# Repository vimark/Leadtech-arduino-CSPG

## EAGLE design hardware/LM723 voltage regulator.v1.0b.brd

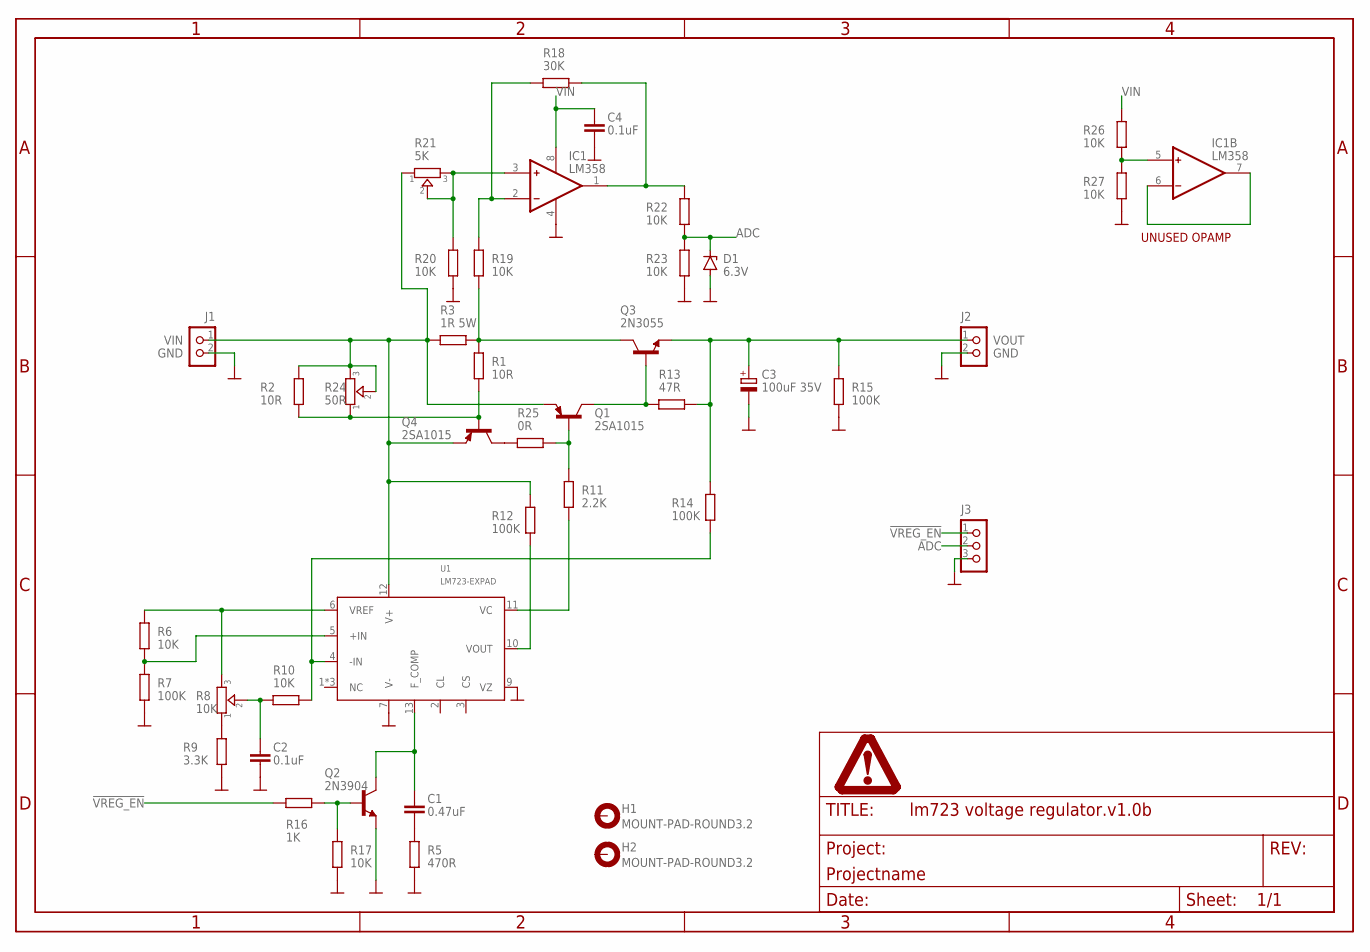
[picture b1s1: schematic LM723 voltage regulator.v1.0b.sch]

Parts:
C1: 0.47uF; C075-042X103
C2, C4: 0.1uF; C075-042X103
C3: 100uF 35V; E2,5-7
D1: 6.3V; DO41Z10
H1, H2: MOUNT-PAD-ROUND3.2; 3,2-PAD
IC1: LM358; DIP8-EXPAD
J1, J2: CON_TERMINAL_BLOCK_02-5MM; TERMINAL_BLOCK_2P_5
J3: CON_HEADER_1X03-PTH; M1X3
PAGE1: FRAME_DINA4_L; DP_LOGO
Q1, Q4: 2SA1015; TO-92
Q2: 2N3904; TO-92
Q3: 2N3055; TO3
R1, R2: 10R; R_5V_EXPAD
R3: 1R 5W; RESISTOR_5W
R5: 470R; R_5V_EXPAD
R6, R17, R19, R20, R22, R23, R26, R27: 10K; R_5V_EXPAD
R7, R12, R14, R15: 100K; R_5V_EXPAD
R8: 10K; TRIMMER_3362P_EXPAD
R9: 3.3K; R_5V_EXPAD
R10: 10K; 0207/12
R11: 2.2K; R_5V_EXPAD
R13: 47R; R_5V_EXPAD
R16: 1K; R-5_EXPAD
R18: 30K; R_5V_EXPAD
R21: 5K; TRIMMER_3362P_EXPAD
R24: 50R; TRIMMER_3362P_EXPAD
R25: 0R; R_5V_EXPAD
U1: LM723-EXPAD; DIP14-EXPAD

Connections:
!VREG_EN: J3.1, R16.1
ADC: D1.C, J3.2, R22.2, R23.1
GND: C2.2, C3.-, C4.2, D1.A, IC1.4 (V-), J1.2, J2.2, J3.3, Q2.1 (E), R5.1, R7.1, R9.1, R15.1, R17.1, R20.2, R23.2, R27.2, U1.7 (V-), U1.9 (VZ)
unnamed: Q3.C, Q3.C/ (C), R1.2, R3.2, R19.2
unnamed: Q4.3 (B), R1.1, R2.1, R24.1
unnamed: Q1.2 (C), Q3.B, R13.1
unnamed: IC1.2 (-), R18.1, R19.1
unnamed: C1.2, R5.2
unnamed: C1.1, Q2.3 (C), U1.13 (F_COMP)
unnamed: R6.1, R7.2, U1.5 (+IN)
unnamed: R6.2, R8.3, U1.6 (VREF)
unnamed: R8.1, R9.2
unnamed: C2.1, R8.2, R10.1
unnamed: R10.2, R14.2, U1.4 (-IN)
unnamed: Q1.3 (B), R11.2, R25.1
unnamed: R11.1, U1.11 (VC)
unnamed: R12.2, U1.10 (VOUT)
unnamed: IC1.3 (+), R20.1, R21.2, R21.3
unnamed: Q2.2 (B), R16.2, R17.2
unnamed: IC1.1 (OUT), R18.2, R22.1
unnamed: Q4.2 (C), R25.2
unnamed: IC1.6 (-), IC1.7 (OUT)
unnamed: IC1.5 (+), R26.2, R27.1
VIN: C4.1, IC1.8 (V+), J1.1, Q1.1 (E), Q4.1 (E), R2.2, R3.1, R12.1, R21.1, R24.2, R24.3, R26.1, U1.12 (V+)
VOUT: C3.+, J2.1, Q3.E, R13.2, R14.1, R15.2

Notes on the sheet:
UNUSED OPAMP

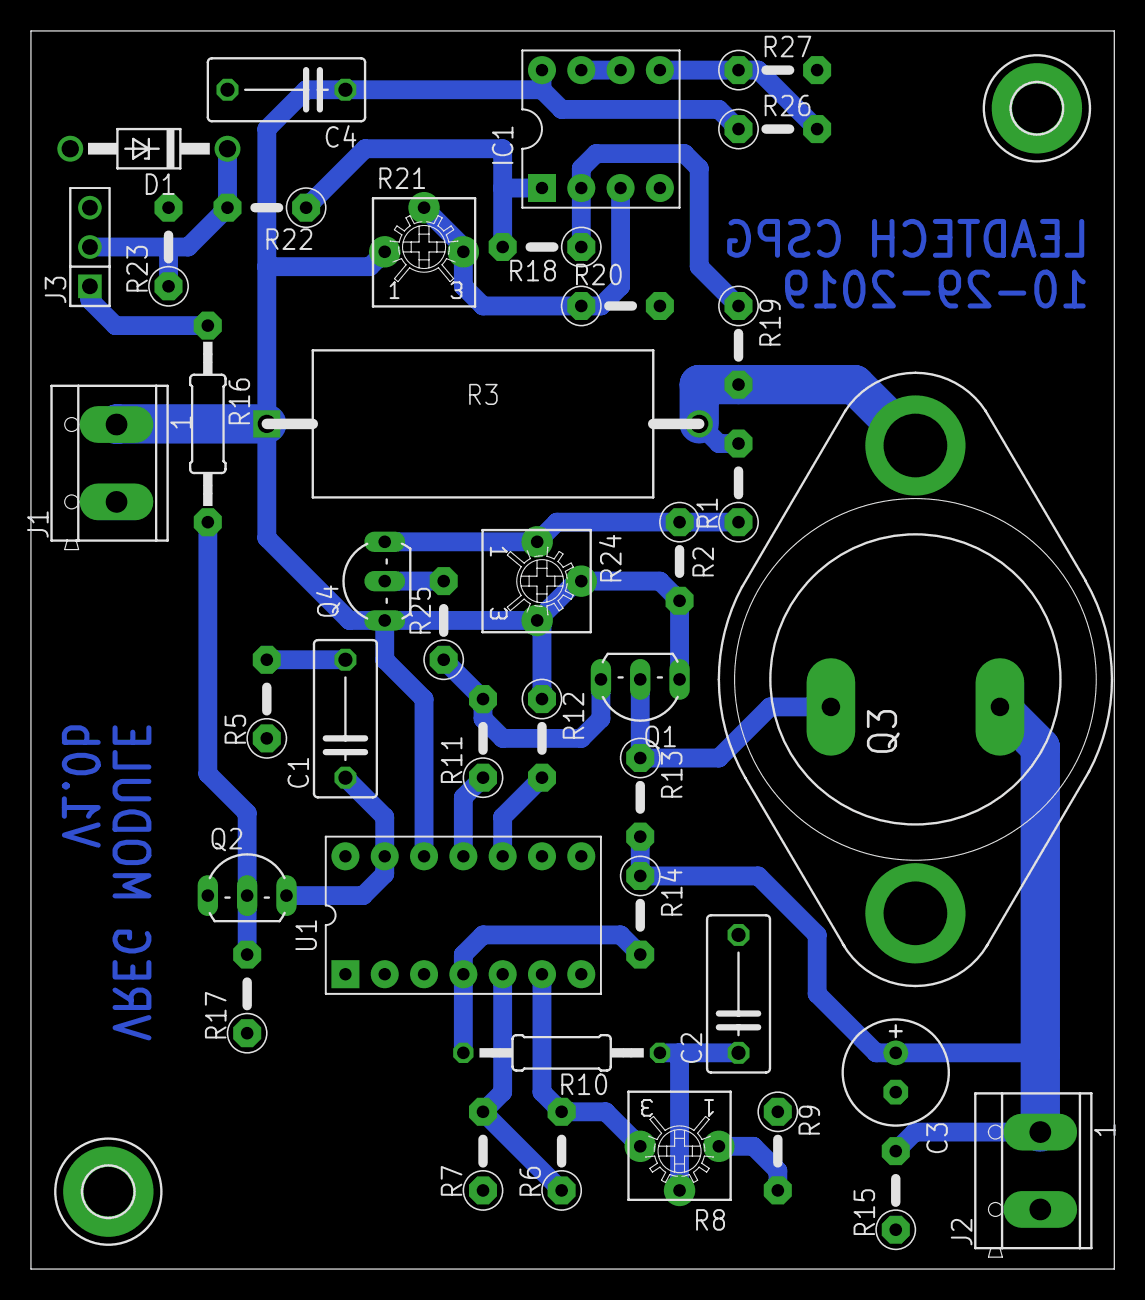
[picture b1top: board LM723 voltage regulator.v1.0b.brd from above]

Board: 2 copper layers, 70.0 x 80.0 mm, 43 parts (0 on the bottom side), 25 nets.

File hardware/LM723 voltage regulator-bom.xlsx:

Qty | Value | Device | Package | Parts | Description | LCSC
2 | 0.1uF | C-EU075-042X103 | C075-042X103 | C2, C4 | CAPACITOR, European symbol | C490602
1 | 0.47uF | C-EU075-042X103 | C075-042X103 | C1 | CAPACITOR, European symbol
1 | 0R | RESISTOR-V | R_5V_EXPAD | R25
4 | 100K | RESISTOR-V | R_5V_EXPAD | R7, R12, R14, R15 |  | C120103 | CF1/4W-100KΩ±5% T52 | CCO(Chian Chia Elec) | 4.875E-3
1 | 100uF 35V | CPOL-EUE2.5-7 | E2,5-7 | C3 | POLARIZED CAPACITOR, European symbol
1 | 10K | R-EU_0207/12 | 0207/12 | R10 | RESISTOR, European symbol | C433778 | RD 1/4W 10K J T/B A1 | TyoHM | 6.0039999999999998E-3
8 | 10K | RESISTOR-V | R_5V_EXPAD | R6, R17, R19, R20, R22, R23, R26, R27 |  | C433778 | RD 1/4W 10K J T/B A1 | TyoHM | 6.0039999999999998E-3
2 | 10R | RESISTOR-V | R_5V_EXPAD | R1, R2 |  | C433800 | RD 1/2WS 10R J T/B A1 | TyoHM RD | 6.0039999999999998E-3
1 | 1K | RESISTOR | R-5_EXPAD | R16
1 | 1R 5W | RESISTOR-5W | RESISTOR_5W | R3 | 22 x 9.5 mm cement resistor
1 | 2.2K | RESISTOR-V | R_5V_EXPAD | R11
1 | 2N3055 | 2N3055 | TO3 | Q3 | NPN Transistor
1 | 2N3904 | TRANSISTOR_BJT_NPN-TO-92-EBC | TO-92 | Q2 | Most commonly used is SOT23-BEC
2 | 2SA1015 | TRANSISTOR_BJT_PNP-TO-92-ECB | TO-92 | Q1, Q4 | Most commonly used is SOT23-BEC
1 | 3.3K | RESISTOR-V | R_5V_EXPAD | R9
1 | 30K | RESISTOR-V | R_5V_EXPAD | R18
1 | 470R | RESISTOR-V | R_5V_EXPAD | R5 |  | C384220 | WR06X471 JTL | Walsin Tech Corp | 2.101E-3
1 | 47R | RESISTOR-V | R_5V_EXPAD | R13
1 | 50R | TRIMMER-3362P_EXPAD | TRIMMER_3362P_EXPAD | R24 | Trimmer resistor | C124583 | 3362P-1-500LF | BOURNS | 0.204545
1 | 5K | TRIMMER-3362P_EXPAD | TRIMMER_3362P_EXPAD | R21 | Trimmer resistor | C81260 | 3362P-1-502LF | BOURNS | 0.21060599999999999
1 | 10K | TRIMMER-3362P_EXPAD | TRIMMER_3362P_EXPAD | R8 | Trimmer resistor | C118956 | 3362P-1-103 | BOCHEN(Chengdu Guosheng Tech) | 0.13120799999999999
1 | 6.3V | 1N4728 | DO41Z10 | D1 | Z DIODE
1 | CON_HEADER_1X03-PTH | CON_HEADER_1X03-PTH | M1X3 | J3
2 | CON_TERMINAL_BLOCK_02-5MM | CON_TERMINAL_BLOCK_02-5MM | TERMINAL_BLOCK_2P_5 | J1, J2 | 2 poles wire to board terminal block
1 | FRAME_DINA4_L | FRAME_DINA4_L | DP_LOGO | PAGE1 | A4 DP frame
1 | LM358 | IC_OP-AMP_LM358-EXPAD | DIP8-EXPAD | IC1 | Dual op-amp | C383852 | TSV358 | Trusignal Microelec | 0.10634299999999999 | SO-8 General Purpose Amplifiers RoHS
1 | LM723-EXPAD | LM723-EXPAD | DIP14-EXPAD | U1 | LM723 Voltage Regulator
2 | MOUNT-PAD-ROUND3.2 | MOUNT-PAD-ROUND3.2 | 3,2-PAD | H1, H2 | MOUNTING PAD, round

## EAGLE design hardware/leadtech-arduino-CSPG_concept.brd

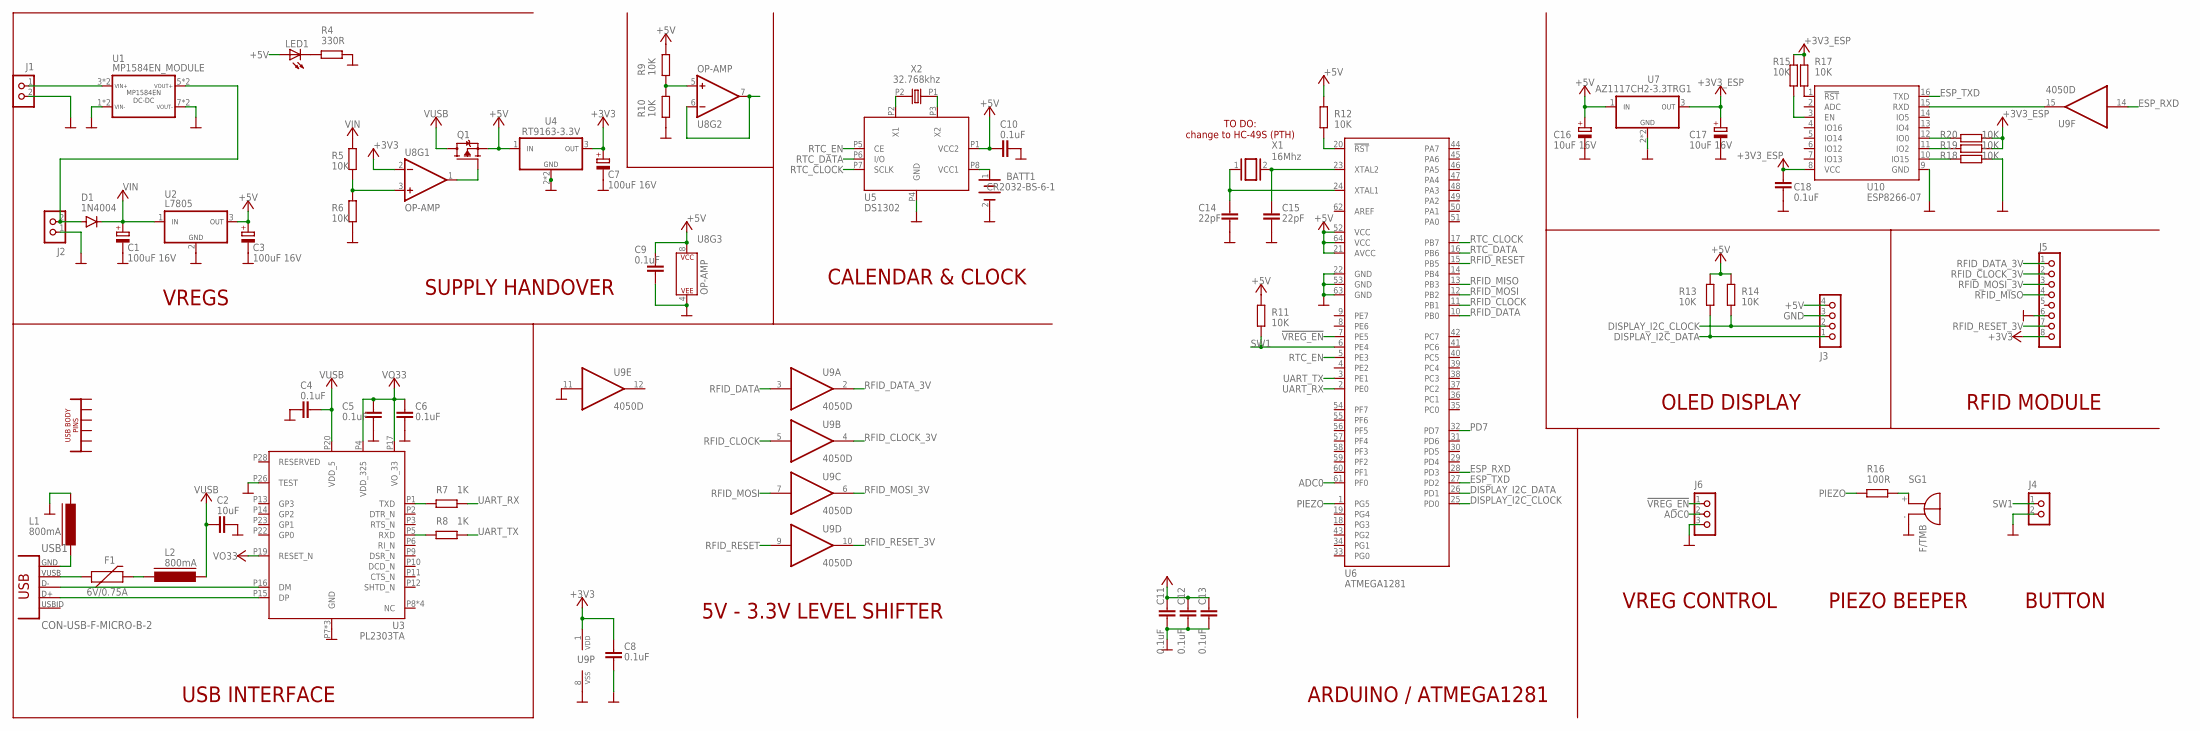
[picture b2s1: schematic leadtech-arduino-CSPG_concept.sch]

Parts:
BATT1: CR2032-BS-6-1; CR2032-BS-6
C1, C3, C7: 100uF 16V; CASE_C
C2: 10uF; C0603
C4, C5, C6, C8, C9, C10, C11, C12, C13, C18: 0.1uF; C0603
C14, C15: 22pF; C0603
C16, C17: 10uF 16V; CASE_B
D1: 1N4004; DO41-10
F1: 6V/0.75A; 1206
J1: CON_HX42003_2; HX42003-2WAF
J2: CON_HEADER_1X02-PTH; M1X2
J3: 2510-4AGW; KF2510-4AGW-2
J4: CON_KF2510-2AGW; KF2510-2AGW
J5: CON_HEADER_1X08-PTH; M1X8
J6: CON_KF2510-3A; KF2510-3A
L1, L2: 800mA; FB805
LED1: LED-0805; LED-805
Q1: TRANSISTOR_FET_TSM2301CX; SOT-23
R4: 330R; R603
R5, R6, R9, R10, R15, R17, R18, R19, R20: 10K; R603
R7, R8: 1K; R603
R11, R12, R13, R14: 10K; R0603
R16: 100R; R0603
SG1: F/TMB
U1: MP1584EN_MODULE; MP1584EN_DCDC_MODULE
U2: L7805; DPAK
U3: PL2303TA; SSOP-28
U4: RT9163-3.3V; SOT-223
U5: DS1302; SOIC-8
U6: ATMEGA1281; TQFP-64
U7: AZ1117CH2-3.3TRG1; SOT-223
U8: OP-AMP; SO08
U9: 4050D; SO16
U10: ESP8266-07
USB1: CON-USB-F-MICRO-B-2; CON_USB_MICRO-B-2-SD-47589-001
X1: 16Mhz; QS
X2: 32.768khz; TC-26

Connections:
!VREG_EN: J6.1, U6.7 (PE5)
+3V3: C7.+, C8.2, J5.8, U4.3 (VOUT), U8.2 (-IN), U9.1 (VDD)
+3V3_ESP: C17.+, C18.2, R15.2, R17.2, R18.1, R19.1, U7.3 (VOUT), U10.8 (VCC)
+5V: C3.+, C9.2, C10.1, C11.1, C12.1, C13.1, C16.+, J3.4, LED1.A, Q1.2 (S), R9.2, R11.2, R12.2, R13.2, R14.2, U2.3 (VOUT), U4.1 (VIN), U5.P1 (VCC2), U6.21 (AVCC), U6.52 (VCC), U6.64 (VCC), U7.1 (VIN), U8.8 (P$V+)
ADC0: J6.2, U6.61 (PF0)
DISPLAY_I2C_CLOCK: J3.2, R14.1, U6.25 (PD0)
DISPLAY_I2C_DATA: J3.1, R13.1, U6.26 (PD1)
ESP_RXD: U6.28 (PD3), U9.14 (I)
ESP_TXD: U6.27 (PD2), U10.16 (TXD)
GND: BATT1.2 (B-), C1.-, C2.1, C3.-, C4.1, C5.2, C6.2, C7.-, C8.1, C9.1, C10.2, C11.2, C12.2, C13.2, C14.1, C15.1, C16.-, C17.-, C18.1, J1.2, J2.1, J3.3, J4.2, J5.6, J6.3, L1.1, R4.2, R6.1, R10.1, R20.1, SG1.-, U1.1 (VIN-), U1.2 (VIN-), U1.7 (VOUT-), U1.8 (VOUT-), U2.2 (GND), U3.P7 (GND), U3.P18 (GND), U3.P25 (GND), U3.P26 (TEST), U4.2 (GND), U4.4 (GND), U5.P4 (GND), U6.22 (GND), U6.53 (GND), U6.63 (GND), U7.2 (GND), U7.4 (GND), U8.4 (P$V-), U9.8 (VSS), U9.11 (I), U10.9 (GND)
unnamed: R17.1, U10.1 (!RST)
unnamed: R15.1, U10.3 (EN)
unnamed: R12.1, U6.20 (!RST)
unnamed: Q1.1 (G), U8.1 (OUT)
unnamed: R5.1, R6.2, U8.3 (+IN)
unnamed: U8.6 (-IN), U8.7 (OUT)
unnamed: J1.1, U1.3 (VIN+), U1.4 (VIN+)
unnamed: C15.2, U6.23 (XTAL2), X1.2
unnamed: R9.1, R10.2, U8.5 (+IN)
unnamed: C14.2, U6.24 (XTAL1), X1.1
unnamed: U3.P16 (DM), USB1.P2 (D-)
unnamed: U3.P15 (DP), USB1.P3 (D+)
unnamed: F1.1, USB1.P1 (VUSB)
unnamed: F1.2, L2.2
unnamed: L1.2, USB1.P5 (GND)
unnamed: R7.1, U3.P1 (TXD)
unnamed: R8.1, U3.P5 (RXD)
unnamed: D1.A, J2.2, U1.5 (VOUT+), U1.6 (VOUT+)
unnamed: R16.2, SG1.+
unnamed: LED1.C, R4.1
unnamed: U5.P3 (X2), X2.P1 (1)
unnamed: U5.P2 (X1), X2.P2 (2)
unnamed: BATT1.1 (B+), U5.P8 (VCC1)
unnamed: R20.2, U10.10 (IO15)
unnamed: R19.2, U10.11 (IO2)
unnamed: R18.2, U10.12 (IO0)
unnamed: U9.15 (O), U10.15 (RXD)
PD7: U6.32 (PD7)
PIEZO: R16.1, U6.1 (PG5)
RFID_CLOCK: U6.11 (PB1), U9.5 (I)
RFID_CLOCK_3V: J5.2, U9.4 (O)
RFID_DATA: U6.10 (PB0), U9.3 (I)
RFID_DATA_3V: J5.1, U9.2 (O)
RFID_MISO: J5.4, U6.13 (PB3)
RFID_MOSI: U6.12 (PB2), U9.7 (I)
RFID_MOSI_3V: J5.3, U9.6 (O)
RFID_RESET: U6.15 (PB5), U9.9 (I)
RFID_RESET_3V: J5.7, U9.10 (O)
RTC_CLOCK: U5.P7 (SCLK), U6.17 (PB7)
RTC_DATA: U5.P6 (I/O), U6.16 (PB6)
RTC_EN: U5.P5 (CE), U6.5 (PE3)
SW1: J4.1, R11.1, U6.6 (PE4)
UART_RX: R7.2, U6.2 (PE0)
UART_TX: R8.2, U6.3 (PE1)
VIN: C1.+, D1.C, R5.2, U2.1 (VIN)
VO33: C5.1, C6.1, U3.P4 (VDD_325), U3.P17 (VO_33), U3.P19 (RESET_N)
VUSB: C2.2, C4.2, L2.1, Q1.3 (D), U3.P20 (VDD_5)

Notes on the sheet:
USB INTERFACE
VREGS
CALENDAR & CLOCK
ARDUINO / ATMEGA1281
RFID MODULE
5V - 3.3V LEVEL SHIFTER
TO DO: change to HC-49S (PTH)
OLED DISPLAY
PIEZO BEEPER
SUPPLY HANDOVER
BUTTON
VREG CONTROL

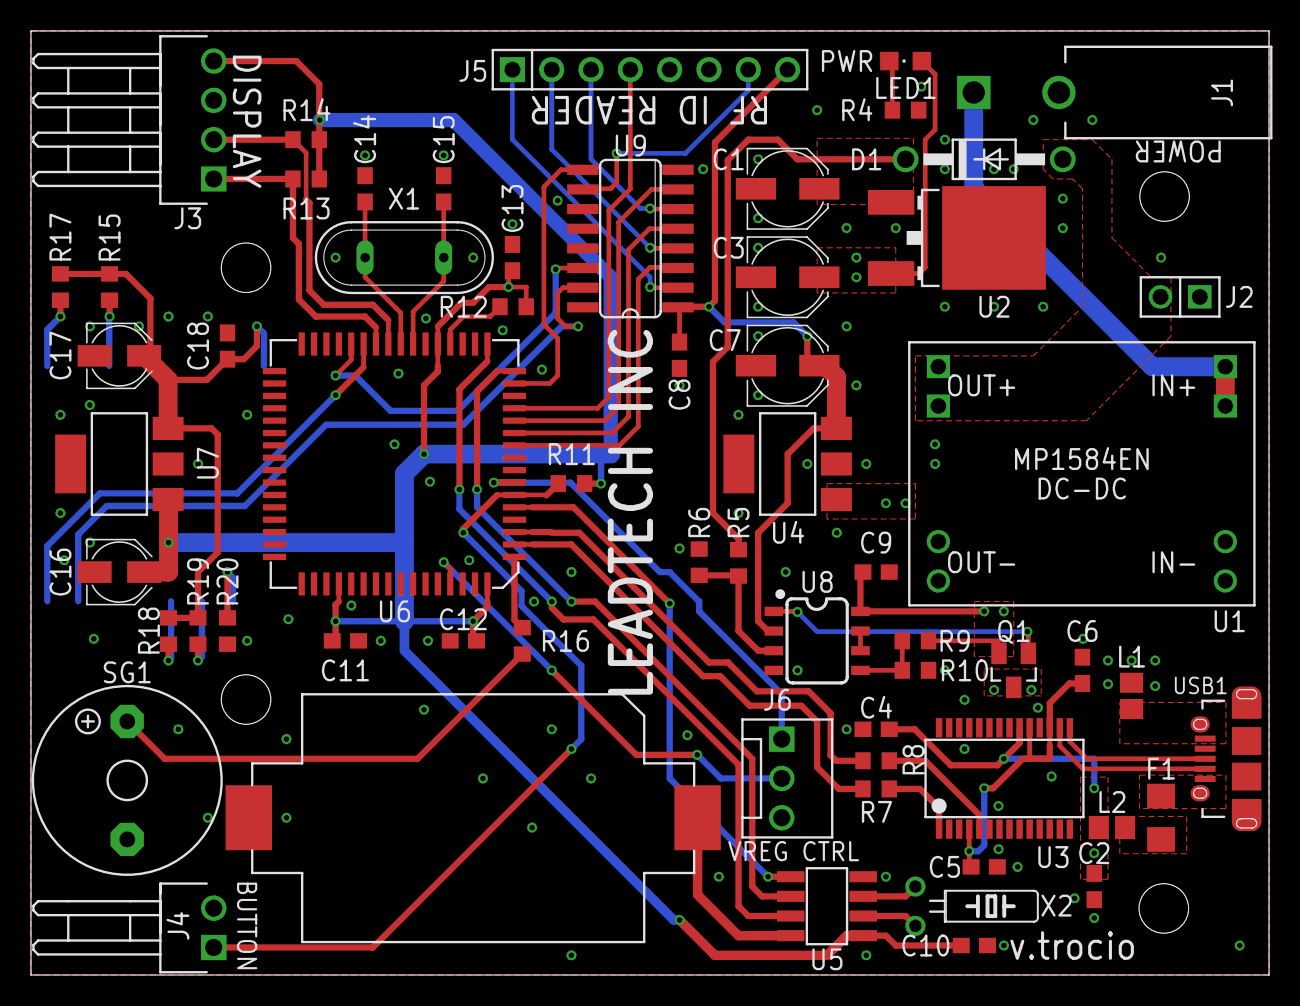
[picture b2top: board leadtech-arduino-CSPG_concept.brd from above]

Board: 2 copper layers, 80.0 x 61.0 mm, 62 parts (1 on the bottom side), 56 nets.

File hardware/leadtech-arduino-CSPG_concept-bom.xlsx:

Qty | Value | Device | Package | Parts | Description | LCSC part no | Mfr no | Brand | Price | Desciption |  | Multiple of 10 | 10
1 |  | LED-0805 | LED-805 | LED1 | Light Emitting Diode | C131244 | 17-21SURC/S530-A2/TR8 | Everlight Elec | 1.4274E-2 |  | 1.4274E-2
1 |  | TRANSISTOR_FET_TSM2301CX | SOT-23 | Q1 | 20V P-Channel Enhancement Mode MOSFET | C375701 | GP2301 | GP(GreenPower) | 3.1213000000000001E-2 |  | 3.1213000000000001E-2
10 | 0.1uF | C-EUC0603 | C0603 | C4, C5, C6, C8, C9, C10, C11, C12, C13, C18 | CAPACITOR, European symbol | C490602 | C0603C104J5RAC | KEMET | 9.2750000000000003E-3 |  | 9.2749999999999999E-2
1 | 100R | R-EU_R0603 | R0603 | R16 | RESISTOR, European symbol | C125923 | AC0603FR-07100RL | YAGEO | 4.202E-3 |  | 4.202E-3
3 | 100uF 16V |  | CASE_C | C1, C3, C7 | Polarized capacitor in various packages | C336761 | EEEFK1C101SR | PANASONIC | 0.171212 |  | 0.51363599999999998
13 | 10K | R-EU_R0603 | R0603 | R11, R12, R13, R14, R5, R6, R9, R10, R15, R17, R18, R19, R20 | RESISTOR, European symbol | C191124 | ERJ3EKF1002V | PANASONIC | 7.8580000000000004E-3 |  | 0.10215400000000001
1 | 10uF | C-EUC0805 | C0603 | C2 | CAPACITOR, European symbol | C76614 | C1608X5R1E106MT000E | TDK | 5.7504E-2 |  | 5.7504E-2
2 | 10uF | CAPACITOR_POL-CASE_B | CASE_B | C16, C17 | Polarized capacitor in various packages | C178278 | EMZA160ADA100MD61G | NCC(Nippon Chemi-Con) | 4.4415000000000003E-2 |  | 8.8830000000000006E-2
1 | 16Mhz | XTAL/S | QS | X1 | CRYSTAL | C114981 | E49A16E00000KE10CO | Hosonic Elec | 0.111524 |  | 0.111524
2 | 1K | RESISTOR-0603 | R603 | R7, R8 |  | C253329 | ESR03EZPJ102 | ROHM Semicon | 1.4148000000000001E-2 |  | 2.8296000000000002E-2
1 | 1N4004 | 1N4004 | DO41-10 | D1 | DIODE | C232435 | 1N4004G | ON Semiconductor | 3.9183999999999997E-2 | 400V 1A 1.1V @ 1A Axial Diodes - General Purpose RoHS | 3.9183999999999997E-2
2 | 22pF | CAPACITOR_NPOL-0805 | C0603 | C14, C15 | Non-Polarized capacitor in various packages | C309441 | AC0603JRNPO9BN220 | YAGEO | 1.6323000000000001E-2 |  | 3.2646000000000001E-2
1 | 2510-4AGW | CON_KF2510-4AGW-2 | KF2510-4AGW-2 | J3 |  | C59729 | 2510-4AGW | BOOMELE(Boom Precision Elec) | 1.8269000000000001E-2 | KF2510 Header Male Pin 0.100"(2.54mm) 4 DIP,P=2.54mm Wire To Board / Wire To Wi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 | 1.8269000000000001E-2
1 | 32.768khz | OSC-XTALTC-26 | TC-26 | X2 |  | C255873 | Q11C02RX1001300 | Seiko Epson | 0.114496 | 32.768KHz ±20ppm 6pF 35 KOhm(Max) Radial,2x6mm Radial Cylinder Crystals RoHS | 0.114496
1 | 330R | RESISTOR-0603 | R603 | R4 |  | C384242 | WR06X331 JTL | Walsin Tech Corp | 1.7930000000000001E-3 |  | 1.7930000000000001E-3
1 | 4050D | 4050D | SO16 | U9 | Hex non-inverting BUFFER | C118326 | HEF4050BT,653 | Nexperia | 0.18030299999999999 |  | 0.18030299999999999
2 | 800mA | FERRITE-0805 | FB805 | L1, L2 | Ferrite bead in various packages | C107330 | MMZ2012S800AT | TDK | 1.8686999999999999E-2 |  | 3.7373999999999998E-2
1 | ATMEGA1281 | ATMEGA1281 | TQFP-64 | U6 |  | C39168 | ATMEGA1281-16AU | Microchip Tech | 7.3939389999999996 | 8-Bit FLASH AVR 16MHz 2.7V ~ 5.5V TQFP-64_14x14x08P ATMEL & AVR RoHS | 7.3939389999999996
1 | AZ1117CH2-3.3TRG1 | VREG-RT9163 | SOT-223 | U7 | 500mA Low Dropout Positive Voltage Regulator | C108492 | AZ1117CH2-3.3TRG1 | Diodes Incorporated | 0.1168 | Fixed 15V 3.3V 800mA SOT-223 Linear Voltage Regulators RoHS | 0.1168
1 | CON_HEADER_1X02-PTH | CON_HEADER_1X02-PTH | M1X2 | J2 | optional |  |  |  |  |  | 0
1 | CON_HEADER_1X08-PTH | CON_HEADER_1X08-PTH | M1X8 | J5 |  | C124416 | C124416 | Ckmtw(Shenzhen Cankemeng) | 9.7434999999999994E-2 | Female Header Female Socket 0.100"(2.54mm) 8 1 Through Hole,P=2.54mm Pin Header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 | 9.7434999999999994E-2
1 | CON_HX42003_2 | CON_HX42003_2 | HX42003-2WAF | J1 | Similar 5569 series | C185087 | HX42003-2WAF | HX(Zhejiang Yueqing Hongxing Elec) | 6.744E-2 | 5569 Header Male Pin 0.118"(3.00mm) 2 Through Hole Wire To Board / Wire To Wire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 | 6.744E-2
1 | CON_KF2510-2AGW | CON_KF2510-2AGW | KF2510-2AGW | J4 | KF2510 alike | C30436 | C30436 | BOOMELE(Boom Precision Elec) | 6.4289999999999998E-3 |  | 6.4289999999999998E-3
1 | CR2032-BS-6-1 | CR2032 | CR2032-BS-6 | BATT1 |  | C70377 | CR2032-BS-6-1 | Q&J | 0.13638400000000001 | SMD Battery Holders, Clips & Contacts RoHS | 0.13638400000000001
1 | DS1302 | DS1302 | SOIC-8 | U5 | Trickle-charge timekeeping chip | C8959 | DS1302Z+T&R | Maxim Integrated | 0.55454499999999995 | Clock/Calendar 31B HH:MM:SS (12/24 hr) YY-MM-DD-dd 3-Wire Serial SOIC-8_150mil 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 | 0.55454499999999995 | 2
1 | ESP8266-07 | ESP8266-07 | ESP8266-07 | U10 | ESP-07 802.11 b/g/n Wi-Fi Module |  |  |  |  |  | 0
1 | F/TMB | F/TMB | F/TMB | SG1 | BUZZER Source: Buerklin | C96093 | TMB12A05 | Jiangsu Huaneng Elec | 0.17448 | Magnetic YES 2300±400Hz 85dB @ 5V, 10cm 5V Φ12mm Through Hole 7.62 Buzzers RoHS | 0.17448
1 | MP1584EN_MODULE | MP1584EN_MODULE | MP1584EN_DCDC_MODULE | U1 |  |  |  |  |  |  | 0
1 | LM358 | LM358 | SO08 | U8 | Generic op-amp footprint | C383852 | TSV358 | Trusignal Microelec | 0.10634299999999999 | SO-8 General Purpose Amplifiers RoHS | 0.10634299999999999
1 | PL2303TA | PL2303TA | SSOP-28 | U3 | USB to serial bridge controller | C8691 | PL2303TA | Prolific Tech | 1.3121210000000001 |  | 1.3121210000000001
1 | RT9163-3.3V | VREG-RT9163 | SOT-223 | U4 | 500mA Low Dropout Positive Voltage Regulator | C150719 | AP7361-33E-13 | Diodes Incorporated | 0.126697 | Fixed 6V 3.3V 1A SOT-223 Low Dropout Regulators(LDO) RoHS | 0.126697
1 | USB micro |  |  | USB1 | USB Female connector | C114094 | 47589-0001 | MOLEX | 0.36060599999999998 |  | 0.36060599999999998
1 | VREG-78M05 | VREG-78M05 | DPAK-3 | U2 | 78M05 | C310413 | L7805CDT-TR | STMicroelectronics | 0.21363599999999999 | Fixed 35V 5V 1.5A TO-252-3 Linear Voltage Regulators RoH | 0.21363599999999999
1 |  |  |  | J6 |  | C29275 | C29275 | BOOMELE(Boom Precision Elec) | 8.8769999999999995E-3 | KF2510 Header Male Pin 0.100"(2.54mm) 3 3P Wire To Board / Wire To Wire Connect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 | 8.8769999999999995E-3 | not added to cart
1 | F1206 |  |  | F1 |  | C183290 | SCF075-1206R | SOCAY | 5.4459E-2 | 8V 1.5A SMD1206 PTC Resettable Fuses RoHS | 5.4459E-2
 |  |  |  |  |  |  |  |  |  | Total | 12.198639

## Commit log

2019-07-27 add doucment sources
2019-08-09 add atmega1281 mcu
2019-08-23 add chip docs
2019-08-23 started routing schematic
2019-08-25 building schematic
2019-08-26 continue wiring schematic
2019-08-28 add project schedule excel, add RFID module on schematic
2019-08-30 continue wiring schematic, RFIF wiring done, level shifter done, add BOM with links on excel sheet
2019-08-30 continue on schematic work, add i2c OLED
2019-09-01 add box plate, i2c oled sketch
2019-09-04 applied changes from kim
2019-09-04 move files around, add readWrite for RFID read/write
2019-09-04 edited box plate drawing, added chip docs
2019-09-06 worked with enclosure design for demo set-up
2019-09-07 small update
2019-09-11 added buzzer function, add circuit for regulated output
2019-09-12 added resources docs
2019-09-13 made some rev on dwg and schematic
2019-09-14 update dwg
2019-09-15 added files
2019-09-16 add card UID writer sketch
2019-09-18 update files
2019-09-21 fix sizes of modules
2019-09-22 upload new references
2019-09-28 added spice sim
2019-09-28 add sketch for RTC
2019-09-28 update on some sketches
2019-10-02 temp note added
2019-10-02 add spice simulations, documents
2019-10-03 fix mounting holes for solar home kit
2019-10-06 small updates
2019-10-07 updated vendor box drawings
2019-10-07 fix cspg vendor sketch
2019-10-07 updates on vendo box
2019-10-08 fix vendor box
2019-10-08 add corel v14 of vendor box laser cutout
2019-10-10 move to do notes to other git repo, fix vendo box design
2019-10-12 add gizduino pins on schematic, add bug comment on value of month on vendor firmware, add time sketches
2019-10-15 fix bug when month is set to greater than 9, add PDF printout of schematic
2019-10-17 fix year display on standby, double the size of load text on printed reciept
2019-10-18 added costing and consting printouts
2019-10-27 made board for LM723, update prepaid metering module placement
2019-10-30 fix circuit and made 2 panelized board
2020-01-01 added new LM723 reference schematic from a known PSU
2020-01-09 varous files updates
2020-01-11 added test result excel
2020-01-31 renamed some docs
2020-02-04 fix grace period when overloaded
2020-02-08 revised prepaid metering front panel text
2020-02-09 added new identification functionality of RFID for each meter, fix time sync via monitor command
2020-02-10 implement card association to its meter, simple command line implementation via serial, configuration saving to RTC ram
2020-02-10 implement serial commands, fix RTC RAM settings partitioning on time out and time rate
2020-02-11 add more serial commands, add eeprom saving
2020-02-12 fix active status bug
2020-02-13 fix buzzer endifs, RTC now works
2020-02-17 added load deletion on vendor firmware, fix current not sensing when card was swiped on client firmware, added censor directives on client firmware
2020-02-18 add kicad under pcb
2020-02-19 wiring and routing under pcb
2020-02-19 board routing donr on under_pcb/patty board
2020-02-20 update results, updated patty board
2020-02-21 edit CSPG arduino hardware
2020-02-22 test result updated for electronic load reading, changed meter user to master user for testing only
2020-02-25 worked on schematic
2020-02-26 separated released firmware folder
2020-02-28 fix serial commands RATE, TIMOUT, working on ID command, add notes on tl494 schematic
2020-03-01 add supply jumper on OLED for patty board
2020-03-01 add power source manager op-amp wiring
2020-03-09 continue routing board
2020-03-09 routing
2020-03-17 done routing, add bom
2020-03-17 making bom
2020-03-18 finish routing main board and bom
2020-03-18 revision on main board

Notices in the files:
parts and their libraries:
dp_devices.v6: LICENSE: CC-BY-SA
SparkFun-IC-Amplifiers: Licensing: Creative Commons ShareAlike 4.0 International - https://creativecommons.org/licenses/by-sa/4.0
